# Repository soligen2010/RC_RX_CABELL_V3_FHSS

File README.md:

# RC_RX_CABELL_V3_FHSS
## Background
RC_RX_CABELL_V3_FHSS is an open source receiver for remote controlled vehicles.  Developed by Dennis Cabell (KE8FZX)
The hardware for this receiver is an Arduino Pro Mini (using a 5V ATMEGA328P at 16 Mhz) and one or two NRF24L01+ modules.  Both are inexpensively available on-line.  Be sure to get the version of a Pro Mini that has pins A4, A5, A6 and A7 broken out.

The transmitter side of this RC protocol is in the Multi-protocol TX Module project at [https://github.com/pascallanger/DIY-Multiprotocol-TX-Module]( https://github.com/pascallanger/DIY-Multiprotocol-TX-Module).

Since there are on-going changes to the main Multi-protocol branch, if you have issues or are using experimental features please test with the solgen2010 fork, which is the latest version tested with the receiver [https://github.com/soligen2010/DIY-Multiprotocol-TX-Module]( https://github.com/soligen2010/DIY-Multiprotocol-TX-Module).

Note: The no-pulses failsafe feature has not yet been merged into pascallanger. Use the soligen2010 fork if you want to use this feature.

## The Protocol
The protocol used is named CABELL_V3 (the third version, but the first version publicly released).  It is a FHSS protocol using the NRF24L01+ 2.4 GHz transceiver.  45 channels are used from 2.403 through 2.447 GHz.  The reason for using 45 channels is to keep operation within the overlap area between the 2.4 GHz ISM band (governed in the USA by FCC part 15) and the HAM portion of the band (governed in the USA by FCC part 97).  This allows part 15 compliant use of the protocol, while allowing licensed amateur radio operators to operate under the less restrictive part 97 rules if desired.

Each transmitter is assigned a random ID (this is handled by the Multi-protocol TX Module) based on this ID one of 362880 possible channel sequences is used for the frequency hopping.  The hopping pattern algorithm ensures that each hop moves at least 9 channels from the previous channel.  One packet is sent every 3 - 4 milliseconds (depending on options chosen), changing channels with each packet. All 45 channels are used equally.

The CABELL_V3 protocol can be configured to send between 4 and 16 RC channels, however this receiver software is currently only capable of outputting up to 8 channels via PWN or PPM.  This is because only 8 channels were conveniently laid out on the Arduino Pro Mini, and more than 8 channels over PPM would be too slow.  SBUS output allows all 16 channels to be used.

I recommend reducing the number of channels as much as possible based on what your model requires.  Fewer channels will use a smaller packet size, which improves transmission reliability (fewer bytes sent means less opportunity for errors).

The protocol also assigns each model a different number so one model setting does not control the wrong model.  The protocol can distinguish up to 255 different models, but be aware that the Multi-Protocol transmitter software only does 16.

## Hardware
A 5V 16Mhz Arduino Pro Mini and one or 2 NRF24L01+ modules are needed for this receiver.  Be sure to get the version of a Pro Mini that has pins A4 and A5 broken out (and A6, A7 too for telemetry analog inputs).  The [hardware folder](https://github.com/soligen2010/RC_RX_CABELL_V3_FHSS/tree/master/hardware) contains a schematic and a PCB layout using a single transceiver module for PWN or PPM output; however, this version of the PCB has not been tested.  I am still using the previous version of the PCB and modifying it to implement the changes included in the new version. If anyone tries this PCB version, please open an issue let me know how it works. 

There is also a schematic for using 2 NRF24L01 modules for diversity.  If anyone designs a board for this, please contribute it.  This schematic also has the signal inverter needed for SBUS.

The PA+LNA versions of the NRF24L01+ module provide more receiver range and reliability than the non PA+LNA versions, However the less expensive modules also work OK if the on-board antenna is replaced with a better antenna, although randomly some units seem to work well and others not so well.  I recommend range testing each module.  These modules are also typically unshielded, but work better when shielded.  Here is an outline of the modifications (TODO: add pictures)

#### Antenna
* For the PA_LNA module that has an SMA Connector, remove the connector. A small butane torch to heat the connector works well.  When the solder melts, it pulls right off 
* Cut the antenna trace.  On the PA+LNA module cut the trace back far enough so that no portion of the trace extends beyond the ground plane on the back of the board.  For the boards with an antenna, cut the trace leading to the antenna shortly after the last surface mount component (a capacitor, I think).
* Scrape or sand away the solder mask over the antenna trace.  On the boards with an antenna you will also need to sand away the area next to the trace for a ground connection.  For the PA+LNA module you can re-use the ground connections that were used for the connector.
* Tin the ground and antenna attachment points with solder
* Strip back the coax and separate the braid, twisting it into a wire that can be soldered to the ground point. Tin this.
* Strip the center conductor back to within 1mm of where the braided part now ends.  Tin this.
* Solder the coax to the board.  Use hot glue to fix the coax to the board as strain relief.
* On the other end of the coax, strip back and remove the braided ground conductor to leave the center wire exposed to form the antenna. Leave the inner wire insulation on.

I am no expert, but based on the best understand I have been able to achieve on the theory, using RG-178 or RG-316 (both have speed factor of 69.5) the calculated theoretical coax lengths to use are:
* For the shielded portion of the coax, ideally make the length a multiple of 42.5 mm.  170mm seems like a good length. 
* The length of the antenna at the end should theoretically be 32.5mm (based on center frequency of 2.425 GHz.  I don’t have the proper equipment to verify these lengths, experiment for what works best for you.  My tests showed 32mm seems to work better than 32.5 for a monopole antenna.

The antennas that come with the PA/LNA modules on EBay are often not very good.  Get a good antenna for your transmitter.  For the transmitter I use a 5dbi antenna constructed as recommend by Andrew McNeil at [https://www.youtube.com/watch?v=bs8hvXGJdhM](https://www.youtube.com/watch?v=bs8hvXGJdhM).  Good RX and TX antennas make a big difference to performance.

#### Shielding
Shielding will require using 2 layers of heat shrink tubing around the whole module.  

* First solder a bare wire onto a ground point on the board.
* Encase as much of the board as possible in heat shrink tubing, leaving the antenna and ground wire sticking out, and don’t cover the pins.
* Use copper tape to wrap the module as much as possible on the heat shrink tubing, while staying away from the edge of the heat shrink. (Aluminum  tape can work too, but you cant solder to it.)
* Bend the ground wire back over the copper tape and solder it to the copper tape.
* Encase as much of the board as possible again in heat shrink tubing.  Don’t cover the pins. Be sure to cover all the ground wire and copper tape shielding.

These shielding steps are based partially  in the article at [http://blog.blackoise.de/2016/02/fixing-your-cheap-nrf24l01-palna-module/](http://blog.blackoise.de/2016/02/fixing-your-cheap-nrf24l01-palna-module/). Using the heat shrink and soldering the copper tape is a more robust implementation of the same concept.

## Receiver Output
The output method is controlled via the option byte in the protocol header.  See the Taranis Setup section for  more details.
* Sum PPM on Arduino pin D2 (the Roll pin). The channel sequence is AETR, more specifically Roll, Pitch, Throttle, Yaw, AUX1, AUX2, AUX3, AUX4.
* Individual PWM channel output on pins D2 through D9 in the sequence Roll, Pitch, Throttle, Yaw, AUX1, AUX2, AUX3, AUX4.
* SBUS (__Experimental__) output on the TX pin through an inverter.  The channel sequence is AETR, more specifically Roll, Pitch, Throttle, Yaw, AUX1, AUX2, AUX3, AUX4, AUX5, AUX6, AUX7, AUX8, AUX9, AUX10, AUX11, AUX12.  SBUS packets are output every 7 milliseconds.

## Receiver Setup
The receiver must be bound to the transmitter. There are several ways for the receiver to enter Bind Mode.  When a receiver is in bind mode the LED will be on.
* A new Arduino will start in bind mode automatically.  Only an Arduino that was flashed for the first time (not previously bound) does this.  Re-flashing the software will retain the old binding unless the EEPROM has been erased.
* Erasing the EEPROM on the Arduino will make it start up in bind mode just like a new Arduino. The Arduino sketch [here]( https://github.com/soligen2010/Reset_EEPROM) will erase the EEPROM.
* Connect the Bind Jumper, or press the Bind button while the receiver powers on.
* The protocol has a Un-bind command (it erases the EEPROM), after which a re-start will cause the receiver to enter bind mode just like a new Arduino. After an Unbind the LED will blink until the receiver is re-started.

Turn on the transmitter and have it send a Bind packet.  The receiver LED changes from always on to a slow blink when the bind is successful.  Re-start the receiver after the bind and take the transmitter out of Bind mode, then test the connection.

## Fail-safe
The receiver fail-safes after 1 second when no packets are received.  If a connection is not restored within 3 seconds then the receiver will disarm.  
* At fail-safe, the throttle is set to minimum, and the other channels are set to the failsafe value.
* After disarm, the throttle will stay at minimum until the receiver is re-armed.  To re-arm the receiver move the throttle to the minimum position.
* If FailsafeNu Pulses is used, then all output signals cease on failsafe (Both PPM and SBUS signals are discontinued)

When a receiver is bound the failsafe values are reset to the default values, which are throttle minimum and all other channels at mid-point.

### Customizing Fail-safe Values
__Do not set fail-safe values while in flight.__  Due to the length of time it takes to write the new fail-safe values to EEPROM, the receiver may go into fail-safe mode while saving the values, causing loss of control of the model.  Before flying a model, always test the fail-safe values after they have been set.

Fail-safe set mode will set the fail-safe values.  This can be done one of two ways:
* A set-Fail-Safe packet can be sent from the transmitter.  The values from the first packet in a series for set-Fail-Safe packets are saved as the new fail-safe values.  The LED is turned on when a set-Fail-Safe packet is received, and stays on as long as set-Fail-Safe packets continue to be received.  The LED is turned off when set-Fail-Safe values stop being received
* After the receiver has initialized, the bind button (or bind jumper) can be held for one to 2 seconds until the LED is turned on.  The values from the first packet received after the LED is turned on will be saved as the new fail-safe values.  The LED will turn off when the button is released (or jumper removed).

When fail-safe set mode is entered, the LED is turned on and stays on until the failsafe set mode is exited.  Only the values from the first packet received in fail-safe set mode are saved (this is to avoid accidentally using up all of the EEPROMs limited number of write operations)

Values for all channels can be set except for the throttle channel.  The fail-safe for throttle is always the minimum throttle.

If the receiver was bound with Failsafe No Pulses, then customizing values does not apply.

## Safety

__Always remove the props when working on a model!__

The receiver has a dis-arm feature to help prevent the motor from unintentionally spinning, however no system is 100%, so take care whenever you power up a model.  __Keep all body parts, clothing, and other objects out of the path of the prop.__

Many ESCs and flight controllers have an arm sequence where the throttle must be set to minimum or some other condition to be met in order to arm.  This receiver also has the following arm/disarm behavior which complements ESC and flight controller arming behavior.

When powered on the __receiver starts out in an armed state__. However, if no signal is detected within 3 seconds the receiver dis-arms.  The receiver also dis-arms if an RC signal is lost for 3 seconds. While dis-armed, only the minimum value will be sent on the throttle channel.  The receiver will re-arm when it receives an RC signal with a minimum value for the throttle channel.  If your model disarms in while in use, move the throttle to its minimum position to re-arm once the RC signal has been re-established.

Powering on the model before the transmitter will cause the receiver to dis-arm in 3 seconds as long as there is no RC signal.  During this power on time there is no output from the receiver until an RC signal is first received from the transmitter, so the ESC or flight controller will not arm if it requires a signal to arm.

Powering the transmitter off before the model will cause the receiver to dis-arm after 3 seconds, forcing the throttle channel to minimum.

There is a 10k pull-up resistor on pin D2 that is essential for safety when using PPM.  This resistor prevents random signals from being output from the receiver while it is initializing.  

### Sending Stick Commands to ESC

__Stay Safe!  Only do this with props removed!__

The reason the receiver initializes in an armed state to to allow an ESC to be configured with stick commands, which may require the initial throttle setting sent to the ESC to be max throttle. If you power on the transmitter before the model, then when the model acquires the signal the values received will be immediately output.  This means that a high throttle will be immediately output.  __Do not do this if your ESC starts in an armed state!__

Please refer to your ESC documentation for details on configuring it with stick commands.

## Diversity
Diversity is achieved by using 2 NRF24L01 modules, which improves link reliability. Try to orient the antennas close to 90 degrees to each other so at least one antenna has a good orientation to the transmitter antenna.  The use of a second NRF24L01 module for diversity is optional.  The code automatically detects if one or 2 modules are connected.  See the "with diversity" schematic in the hardware folder for how to wire the NRF24L01 modules.

Both modules listen for an incoming packet.  If the primary receiver does not get a packet when expected, the secondary receiver is checked for the missed packet.  After each packet, the primary/secondary receivers are swapped, except in the case where only the primary receiver had the packet, in which case this receiver will retain the primary role.  Telemetry packets are transmitted using the same receiver that was used to read the packet.  If both receivers got the incoming packet, then the packet in the secondary receiver is discarded.  The net effect is that the receivers alternate with each packet, except when only one receiver is receiving, in which case that receiver continues to be used for both the primary receiver and telemetry transmit.

## Taranis Setup using Multi-Protocol Module and Open-TX 2.2

With a Multi Protocol module installed in the Taranis, this is how to configure a model to use this protocol.  These instructions for for a Serial connection using OpenTX 2.2.  These instructions assume some familiarity with using OpenTX on the Taranis.

### Initial Setup 
   
* Press Menu to go to Model Selection and Select the model you with to set up.
* Press Page to get the the Model Setup page.
* Scroll down to the Internal RF section and change Mode to OFF.
* Scroll down to the External RF section and change Mode to MULT.
* In the protocol field to the right of MULT, select Custom.
* In the protocol field to the right of Custom, enter 34.  This is the protocol number. 
  * __This number is temporary.  It likely will need to change when the TX half of this protocol is merged into the main Multi-Protocol project.__
* The next number to the right is the sub-protocol.  For initial setup select 0 or 1.  Valid values are:
  * 0 - Normal usage without telemetry
  * 1 - Normal usage with telemetry (please see the section on telemetry)
  * 6 - Set fail-safe values (see below and the Fail-safe section)
  * 7 - Unbind receiver (see below)
* Receiver No. should be filled in with the model number.
* Move down to the Option value.  This value must be calculated to configure the protocol.  This is done by entering a number that is the sum of the options you wish to use.  Select the values from below and add them together to get the option value.
  * _Channel Reduction_ reduces the number of channels transmitted.  This also reduces the size of the packet, which improves reliability. (Fewer bytes sent equates to less opportunity for error.)  For best reliability reduce the number of channels to the minimum number needed for the model. Note that at least 4 channels must always be sent.  Choose one of the following to add into the Option value:
    * 0  - Send 16 channels
    * 1  - Send 15 channels
    * 2  - Send 14 channels
    * 3  - Send 13 channels
    * 4  - Send 12 channels
    * 5  - Send 11 channels
    * 6  - Send 10 channels
    * 7  - Send 9 channels
    * 8  - Send 8 channels
    * 9  - Send 7 channels
    * 10 - Send 6 channels
    * 11 - Send 5 channels
    * 12 - Send 4 channels
  * _Output Mode_ indicates how the receiver should output the channels.  Choose one of the following to add into the Option value:
    * 0  - Output servo PWM signals on pins D2 through D9 for channels 1 to 8
	* 16 - Output channels 1 to 8 using PPM on pin D2
	* 32 - Output channels 1 to 16 using SBUS __(Experimental)__
  * _Transmitter Power_ Overrides the Multi-Protocol's normal high power setting.  See comments on power setting below.  Choose one of the following to add into the Option value:
    * 0 - Use the NRF24L01+ HIGH power setting.  This is the normal Multi-Protocol module behavior.
    * 64 - Use the NRF24L01+ MAX power setting instead of the HIGH power setting.  This over-rides the normal Multi-Protocol module behavior.
  #### Notes on Power Setting
  Using an NRF24L01+ with PA/LNA outputs 25 milliwatts for HIGH power and 100 milliwatts for MAX power.  Despite this there are reports that using MAX power on inexpensive Chinese modules provides worse range than using the HIGH power setting due to the noise added by the extra amplification and the lower quality Chinese components.  By adding shielding and using a good antenna, I get better range using MAX power even with Chinese components.  Your results may vary so range test your equipment and use the setting that provides the best results.

### Binding Receiver
* Turn on the receiver in Bind Mode. (See receiver setup above.)
* In the transmitter Navigate to the Model Setup page.
* In the External RF section, highlight BIND and press enter.
* The receiver LED will blink when the bind is successful.
* Restart the receiver.
 
### Unbinding Receiver

In order to un-bind a receiver using the transmitter, a model bound to the receiver must be configured in the transmitter.  With a model selected that is bound to the receiver:
* Navigate to the Model Setup page.
* Go to the External RF section.
* Change the sub-protocol (second number after "Custom") to 7.
* The receiver LED will fast blink when the un-bind is successful.
When the receiver is restarted, it will start in Bind mode.

### Setting Failsafe Values

__Do not set fail-safe values while in flight.__ Please see the Customizing Fail-safe Values section for more information.

* Navigate to the Model Setup page.
* Go to the External RF section.
* Place all switches in the desired fail-safe state.
* Move the sticks to the desired fail-safe state.  Hold them in this position until the fail-safe settings are recorded by the receiver.
* While holding the sticks, change the sub-protocol (second number after "Custom") to 6.  DO not go past 6.  If you even briefly go to 7 the receiver will un-bind.
* When the LED is turned on, the Fail-safe settings are recorded
* Change the sub-protocol back to its original setting. The LED will turn off.

Always test the Fail-safe settings before flying.  Turning off the transmitter should initiate a Fail-safe after one second.

### Setting Failsafe No Pulses (Experimental)

Failsafe No Pulses can only be set at bind time.  All servos will receive no pulses during a fail-safe, so custom fail safe values do not apply.  If the receiver is on SBUS output mode, the SBUS output is stopped during failsafe.

* Unbind the receiver.
* Navigate to the Model Setup page.
* Go to the External RF section.
* Change the sub-protocol to 5.  
* Perform the Bind procedure.
* Change the sub-protocol to the desired setting for flying.

If your output goes to a flight controller via SBUS, and the flight controller honors the SBUS failsafe flag (which is typical), then you probably do not want to use No Pulses because the SBUS protocol handles the failsafe appropriately.

Always test the Fail-safe settings before flying.  Turning off the transmitter should initiate a Fail-safe after one second.

## Telemetry

When the sub-protocol is set to Normal with Telemetry, the receiver sends telemetry packets back to the transmitter.  Three values are returned, a simulated RSSI, and the voltages on the Arduino pins A6 and A7.  A receiver module with diversity is recommended when using telemetry to increase the reliability of the telemetry packets being received by the transmitter.

### RSSI

Because the NRF24L01 does not have an RSSI feature, the RSSI value is simulated based on the packet rate.  The base of the RSSI calculation is the packet success rate from 0 to 100.  This value is re-calculated approximately every 1/2 second (every 152 expected packets).  This success percentage is then modified in real time based on packets being missed, so that if multiple packets in a row are missed the RSSI value drops without having to wait for the next re-calculation of the packet rate.

In practice, the packet rate seems to stay high for a long range, then drop off quickly as the receiver moves out of range.  Typically, the telemetry lost warning happens before the RSSI low warning.

The RSSI class encapsulates the RSSI calculations. If you are so inclined, feel free play with the calculation. If anyone finds an algorithm that works better, please contribute it. 

### Analog Values

Analog values are read on Arduino pins A6 and A7.  Running on a, Arduino with VCC of 5V, only values up to 5V can be read.  __A value on A6 or A7 that exceeds the Arduino VCC will cause  damage__, so care must be taken to ensure the voltage is in a safe range.

Values from pins A6 and A7 come into a Taranis transmitter as telemetry values A1 and A2.  You can use either of these to read battery voltage or the output of current sensor.  The following article explains how to input battery voltage to A2 on an Frsky receiver using a voltage divider.  The same method can be used to read battery voltage on this receiver.  [http://olex.biz/tips/lipo-voltage-monitoring-with-frsky-d-receivers-without-sensors](http://olex.biz/tips/lipo-voltage-monitoring-with-frsky-d-receivers-without-sensors).

The values sent are 0 - 255 corresponding to 0V - 5V.  This will need to be re-scaled to the actual voltage (or current, etc.) in the transmitter on the telemetry  configuration screen.

## Flashing Firmware

The Arduino development environment is required to compile the code and write the firmware to the Arduino Pro Mini. If you are not familiar with this, here are some resources to help you.

* [https://www.arduino.cc/en/Guide/HomePage](https://www.arduino.cc/en/Guide/HomePage)
* [https://www.arduino.cc/en/Guide/ArduinoProMini](https://www.arduino.cc/en/Guide/ArduinoProMini)
* [https://www.youtube.com/watch?v=78HCgaYsA70](https://www.youtube.com/watch?v=78HCgaYsA70)
* [http://lab.dejaworks.com/programming-arduino-mini-pro-with-ftdi-usb-to-ttl-serial-converter/](http://lab.dejaworks.com/programming-arduino-mini-pro-with-ftdi-usb-to-ttl-serial-converter/)

## Receiver Test Harness

The receiver code can be compiled as a test harness.  What this means is that instead of outputting the normal output signals, statistics are displayed on a 16x2 LCD screen about the packet success rate. To enable Test Harness mode, uncomment the following line in TestHarness.h.  No output will go to servos, flight controller, etc. when in test harness mode.

```//#define TEST_HARNESS```

The LCD displays 5 numbers.
* Line 1:  Packet success rate (percent); Number of missed packets in a row; The number of time the secondary receiver  recovers a packet the primary receiver  missed
* Line 2:  The number of good packets received; The number of missed or bad packets

The LCD pin connections are:

  LCD D4_PIN = Arduino D9
  LCD D5_PIN = Arduino D8
  LCD D6_PIN = Arduino D7
  LCD D7_PIN = Arduino D6
  LCD RS_PIN = Arduino D5
  LCD EN_PIN = Arduino D4
  
More information on connecting the LCD is at [https://www.arduino.cc/en/Tutorial/LiquidCrystalDisplay](https://www.arduino.cc/en/Tutorial/LiquidCrystalDisplay).  However, I suggest using a 330 or 470 ohm resistor instead of the 220 ohms listed in the article to avoid pulling over 20 mA from the Arduino pin connected to the LED back-light.

You can also connect an I2C LCD display.  This may require additional code editing and the installation of a different LCD library (from [https://bitbucket.org/fmalpartida/new-liquidcrystal/downloads/](https://bitbucket.org/fmalpartida/new-liquidcrystal/downloads/)).  Please see the comments in TestHarness.h for more details.

## Packet Format

```
typedef struct {
   enum RxMode_t : uint8_t {   
         normal                 = 0, 
         bind                   = 1,
         setFailSafe            = 2,
         normalWithTelemetry    = 3,  
         telemetryResponse      = 4,
         bindFalesafeNoPulse    = 5,   (experimental)
         unBind                 = 127
   } RxMode;
   uint8_t  reserved = 0; /* Contains the channel number that the packet was sent on in bits 0-5 
                          */
   uint8_t  option;
                          /*   mask 0x0F    : Channel reduction.  The number of channels to not send (subtracted from the 16 max channels) at least 4 channels are always sent.
                           *   mask 0x30>>4 : Receiver output mode
                           *                  0 (00) = Single PPM on individual pins for each channel 
                           *                  1 (01) = SUM PPM on channel 1 pin
                           *                  2 (10) = SBUS output
                           *                  3 (11) = Unused
                           *   mask 0x40>>6   Contains max power override flag for Multiprotocol TX module. Also sent to RX
                           *                  The RX uses MAX power when 1, HIGH power when 0
                           *   mask 0x80>>7   Unused 
                           */  
   uint8_t  modelNum;
   uint8_t  checkSum_LSB;   // Checksum least significant byte
   uint8_t  checkSum_MSB;   // Checksum most significant byte
   uint8_t  payloadValue [24] = {0}; //12 bits per channel value, unsigned
} CABELL_RxTxPacket_t;   
```
Each 12 bits in payloadValue is the value of one channel.  The channel order is EART (i.e. Pitch, Roll, Yaw, Throttle, AUX1, AUX2, AUX3, AUX4).  Valid values are in the range 1000 to 2000.  The values are stored big endian.

Using channel reduction reduces the number of bytes sent, thereby trimming off the end of the payloadValue array.

## Credits
davidbuzz on github.  Although none of his code is in this project, my very first foray into DIY rx/tx was based on his esp8266_wifi_tx project.

iforce2d on YouTube.  Although none of his code is in this project, the work he did with the NRF24L01 was a big inspiration.

All the contributors to the pascallanger/DIY-Multiprotocol-TX-Module project on GitHub.  This is a great contribution to the RC community and houses the TX side of this protocol.  

All the contributors to the nRF24/RF24 project on GitHub.  This library was essential to learning to use the NRF24L01.

All the contributors to Arduino Core and standard libraries.  Especially the Servo library, which I modified to adapt to the needs of this project.

The author of the PPM algorithm at https://code.google.com/archive/p/generate-ppm-signal/ I believe this to be david.hasko94@gmail.com

The channel sequence is generated using a permutation algorithm described at http://stackoverflow.com/questions/7918806/finding-n-th-permutation-without-computing-others 

Nick Gammon for his tutorials on interrupts and async reading of ADC pins at https://www.gammon.com.au/adc

My wife, for tolerating the obsession I have had with this project.

## License Info
Copyright 2017 - 2019 by Dennis Cabell (KE8FZX)
 
To use this software, you must adhere to the license terms described below, and assume all responsibility for the use of the software.  The user is responsible for all consequences or damage that may result from using this software. The user is responsible for ensuring that the hardware used to run this software complies with local regulations and that any radio signal generated from use of this software is legal for that user to generate.  The author(s) of this software assume no liability whatsoever.  The author(s) of this software is not responsible for legal or civil consequences of using this software, including, but not limited to, any damages cause by lost control of a vehicle using this software.   If this software is copied or modified, this disclaimer must accompany all copies.
 
This project is free software: you can redistribute it and/or modify it under the terms of the GNU General Public License as published by the Free Software Foundation, either version 3 of the License, or (at your option) any later version.

RC_RX_CABELL_V3_FHSS is distributed in the hope that it will be useful, but WITHOUT ANY WARRANTY; without even the implied warranty of MERCHANTABILITY or FITNESS FOR A PARTICULAR PURPOSE.  See the GNU General Public License for more details.

You should have received a copy of the GNU General Public License along with RC_RX_CABELL_V3_FHSS.  If not, see <http://www.gnu.org/licenses/>.

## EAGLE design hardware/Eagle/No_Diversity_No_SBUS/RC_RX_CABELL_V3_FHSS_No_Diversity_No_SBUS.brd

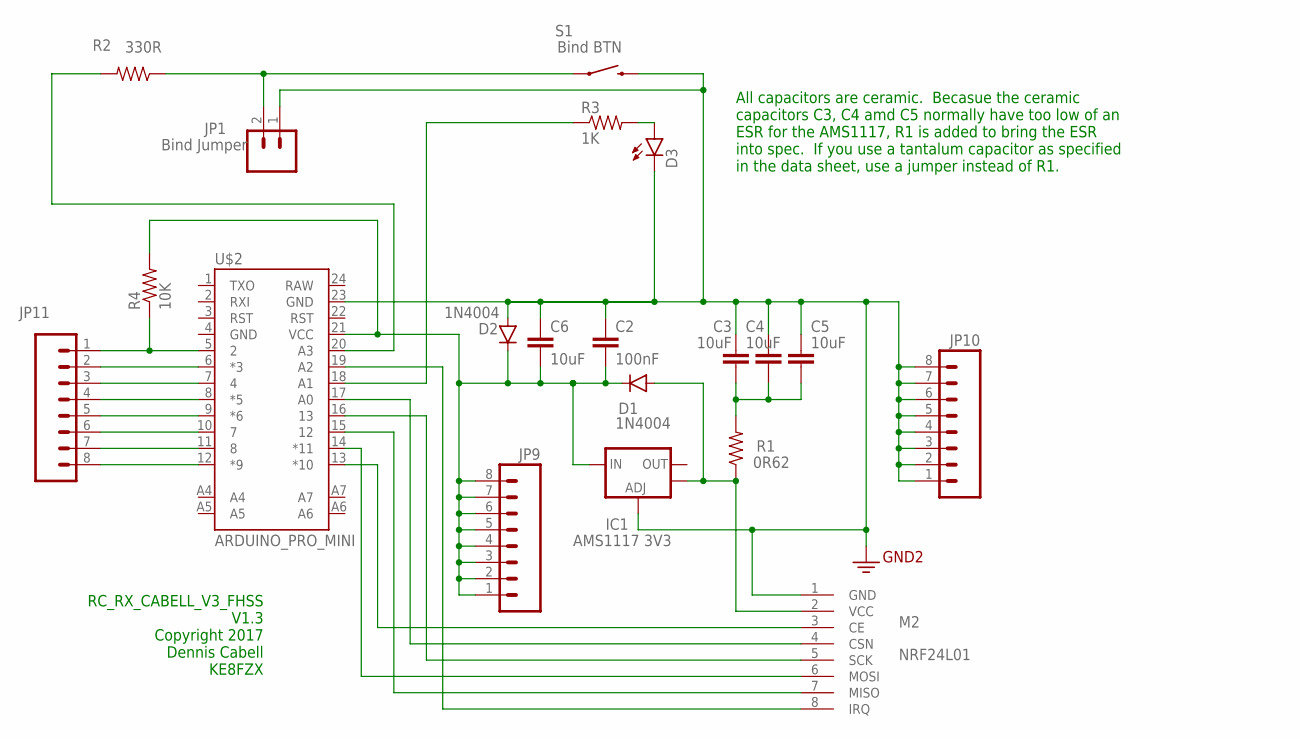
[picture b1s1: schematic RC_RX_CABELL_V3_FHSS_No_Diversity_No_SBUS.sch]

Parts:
C2: 100nF; CAP-PTH-5MM
C3, C4, C5, C6: 10uF; CAP-PTH-5MM
D1, D2: 1N4004; DIODE-1N4001
D3: LED3MM
IC1: AMS1117 3V3; SOT223
JP1: Bind Jumper; 1X02
JP9, JP10, JP11: M08; 1X08_ROUND
M2: NRF24L01; WIRELESS-NRF24L01
R1: 0R62; AXIAL-0.5
R2: 330R; AXIAL-0.3
R3: 1K; AXIAL-0.3
R4: 10K; AXIAL-0.3
S1: Bind BTN; TACTILE-SWITCH-1101NE
U$2: ARDUINO_PRO_MINI

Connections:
5V: C2.2, C6.2, D1.C, D2.C, IC1.3 (IN), JP9.1, JP9.2, JP9.3, JP9.4, JP9.5, JP9.6, JP9.7, JP9.8, R4.P$2 (2), U$2.21 (VCC)
GND: C2.1, C3.1, C4.1, C5.1, C6.1, D2.A, D3.K (C), IC1.1 (ADJ), JP1.1, JP10.1, JP10.2, JP10.3, JP10.4, JP10.5, JP10.6, JP10.7, JP10.8, M2.1 (GND), S1.2, U$2.23 (GND)
unnamed: JP11.1, R4.P$1 (1), U$2.5 (2)
unnamed: M2.3 (CE), U$2.13 (*10)
unnamed: JP11.2, U$2.6 (*3)
unnamed: JP11.3, U$2.7 (4)
unnamed: JP11.4, U$2.8 (*5)
unnamed: JP11.5, U$2.9 (*6)
unnamed: JP11.6, U$2.10 (7)
unnamed: JP11.7, U$2.11 (8)
unnamed: JP11.8, U$2.12 (*9)
unnamed: JP1.2, R2.P$1 (1), S1.1
unnamed: M2.8 (IRQ), U$2.19 (A2)
unnamed: C3.2, C4.2, C5.2, R1.P$2 (2)
unnamed: M2.5 (SCK), U$2.16 (13)
unnamed: M2.4 (CSN), U$2.17 (A0)
unnamed: D3.A, R3.P$2 (2)
unnamed: M2.6 (MOSI), U$2.14 (*11)
unnamed: R3.P$1 (1), U$2.18 (A1)
unnamed: M2.7 (MISO), U$2.15 (12)
unnamed: R2.P$2 (2), U$2.20 (A3)
VCC: D1.A, IC1.4 (OUT), M2.2 (VCC), R1.P$1 (1)

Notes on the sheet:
RC_RX_CABELL_V3_FHSS V1.3 Copyright 2017 Dennis Cabell KE8FZX
All capacitors are ceramic. Becasue the ceramic capacitors C3, C4 amd C5 normally have too low of an ESR for the AMS1117, R1 is added to bring the ESR into spec. If you use a tantalum capacitor as specified in the data sheet, use a jumper instead of R1.

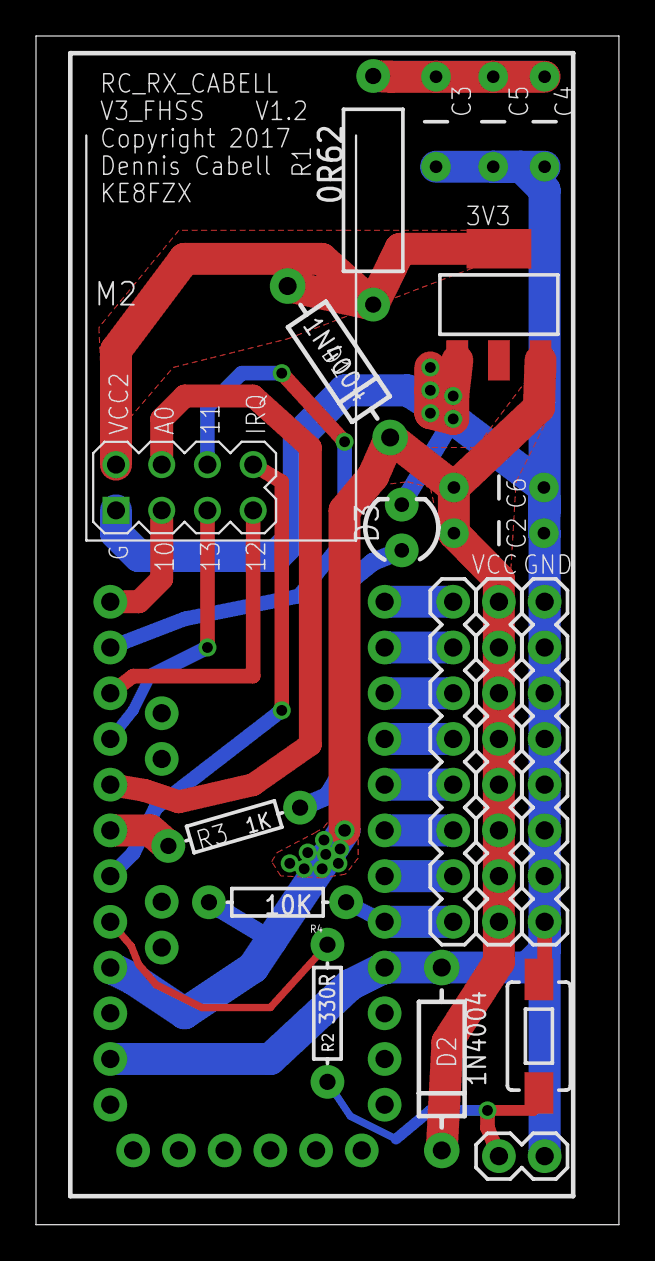
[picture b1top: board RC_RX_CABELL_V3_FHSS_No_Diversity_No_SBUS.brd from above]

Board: 2 copper layers, 32.4 x 66.0 mm, 20 parts (0 on the bottom side), 22 nets.

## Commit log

2017-03-11 First Public Version
2017-03-11 Noted tranmitter code not yet merged with Multiprotocol
2017-03-11 FIxed typos
2017-03-11 Formatting
2017-03-11 fixed comment typos
2017-03-15 Opened up a bit in the option byte for future use
2017-03-15 Fixed bug in processing unBind command from TX
2017-03-25 Support 1Mbps (auto detect) and telemetry stubs
    Syncing to the transmitter signal will alternate between 1Mbps and
    250kbps until the FHSS signal is locked in, then data raqte is retained
    until teh signal is lost of a re-sync needs to happen.
2017-04-11 Changed Bind pin to A3, Added Eagle files
    This frees A4 for potential use of I2C bus in the future
2017-04-13 Fixed compile issue in arduino 1.6.8
2017-04-13 comments about encoder library
2017-04-13 Added RSSI calculation
2017-04-16 RSSI Telemetry Response
    RSSI telemetry is being sent and successfully recieved by TX
2017-04-16 SUM_PPM constrain channel value to valid range
2017-04-16 SUM_PPM constrain max PPM channels to 8 to ensure fits frame size
2017-04-16 Documentation Update
2017-04-19 Analog telemetry from A6/A7, Telemetry packet Xmits sooner, Checksum field split to avoid endian issue
2017-04-21 Updated packet layout comments
2017-04-25 Removed non-IRQ operation in favcor of IRQs
    REmoved entirely polling the NRF24l01 as polling during RX or TX might
    cause reliability issue.
2017-05-02 Tweaked packet timing
2017-05-02 Pass packet structure by reference
2017-05-02 Read analog pins asynchonously with interrupt
2017-05-02 Moved RxMOde bit flip to proper place
2017-05-02 Re-arm thottle if within 10 of min value (within 1%)
2017-05-02 typos fixed in comments
2017-05-02 Completion of async adc code
2017-05-07 RSSI max 100; Async analog reads; ISR streamlined
2017-05-12 Reduced servo jitter
    Turned off timer0 ISR and replaced with time functions that dont use
    ISRs
2017-05-12 Disarm throttle one second after startup if no signal recieved
2017-05-12 Removed use of ClickEncoder library in favor of smaller function
2017-05-12 Honor the MAx Power Override bit in the option byte when sending telemetry packets
2017-05-14 Removed myMicros - going back to arduino micros()
    myMicros turned out to be unreliable. Using micros() is much more
    reliable. We will just have to tolerate the little bit of servo jitter
    this may cause.
2017-05-14 Removed myMicros - going back to arduino micros()
2017-05-18 Added radio diversity
    2 NRF24L01 modules can be used to improve link reliability.
2017-05-18 Diversity Recievers
2017-05-18 Schematic with Diversity
2017-05-21 Test harness option and RSSI caclulation revamp
2017-05-29 Improved loop timing; telemetry returns sooner; telemetry at 250 kbps
    Teh RF24 library is now also embedded in the project to it sould be
    modified specifc to this project
2017-05-31 SBUS skeleton added
2017-06-01 Change MyServo.writeMicroseconds to only disable interrupts and change the ticks if teh value actually changed
    channels 4 to 8 rarely change packet to packet, so this reduces time
    spent with interrupts disabled
2017-06-01 Disable interrupts when updating SUM PPM values, but not of the value hasnt changed
2017-06-02 Calibrated and PPM and optimized the PPM ISR
2017-06-03 SBUS Serial Output and packet timing
2017-06-04 Avoid Serial.print when on SBUS mode becasue SBUS used UART
2017-06-10 Updated diversity scematic for SBUS
2017-06-11 Removed code for 1Mbps. 250kbps is more reliable
2017-06-11 Added option for I2C LCD for Test Harness
2017-06-11 Added chaeck for a False Signal Lock and re-sync when detected.
2017-06-11 Added check for False Signal Lock and re-sync when detected,
2017-06-13 Corrected packet timing when secondary reciever used
2017-06-17 Hardware Updates for SBUS & PPM
2017-06-18 Fully reset test harness display after failsafe/resync
2017-06-18 Multiprotocol proticol number is now 34
2017-06-18 Hardware folder link
2017-06-21 Corrected output mode numbers
2017-06-24 SBUS is now working
2017-06-24 Calibrated PPM using betaflight on F4 board
2017-08-10 Fix typos in comments
2017-08-10 Comment Typos; More stringent signal lock on power on.
    First time syncing teh hopping when powered on be more stringent. Must
    have stong signal on all 45 channels to lock in signal for first time.
    After initial lock use the previous less stringent method. This is to
    help ensure a strong lock on power up when initially connecting model to
    transmitter.
2017-08-10 increased resync timeout to 3 sec
2017-08-10 Tweak Initial signal lock logic
2017-08-10 Wait for conversions to finish on initializing ADC calls
2017-09-05 Test harness Serial message on boot
2017-10-14 Testharness doesn't repeatedly display Re-sync
    In some cases when Re-syncing while in test harness mode the LCD was
    constantly being refreshed. This change displays the Re-sync message
    only once.
2017-11-30 The TX side is now accepted in the Multiprotocol project
    Updated Readme
2018-01-28 Option Safety for a ESC with reverse gear
2018-01-28 Updapte Readme
2019-01-21 Fixed case of includes
    needed for compiling on Linux
2019-01-21 Get current channel from reserved byte
    At close range the packet can be recieved on an adjacent channel. This sets the current channel to the channel teh TX sent the packet on so the correct next channel is calculated.
2019-01-21 Get Current Channel from Reserved Byte
    and formatting changes
2019-01-21 CurrrentChannel Fix
2019-01-21 CurrentChannel Fix
2019-01-21 Added No Pulses Failsafe
    Experimental
2019-01-23 Comment Updates
2019-01-23 Seperate #define for CE pins set = csn pin
2019-01-23 EAsier to set custom throttle value for disarmed state
    THROTTLE_DISARM_VALUE added to RX.h
2019-01-24 Update TestHarness.h
    fix anoying special character at end of file
2021-11-09 Reset RSSI packet-miss count after reporting it. Keeps previous misses from masking recent signal improvements.

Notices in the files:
README.md:
License Info:
Copyright 2017 - 2019 by Dennis Cabell (KE8FZX)
To use this software, you must adhere to the license terms described below, and assume all responsibility for the use of the software.  The user is responsible for all consequences or damage that may result from using this software. The user is responsible for ensuring that the hardware used to run this software complies with local regulations and that any radio signal generated from use of this software is legal for that user to generate.  The author(s) of this software assume no liability whatsoever.  The author(s) of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
